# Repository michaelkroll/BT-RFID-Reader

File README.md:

BT-RFID-Reader
==============

BT-RFID-Reader Eagle design files, Arduino Sketch, WT-12 Config and 3D Enclosure files

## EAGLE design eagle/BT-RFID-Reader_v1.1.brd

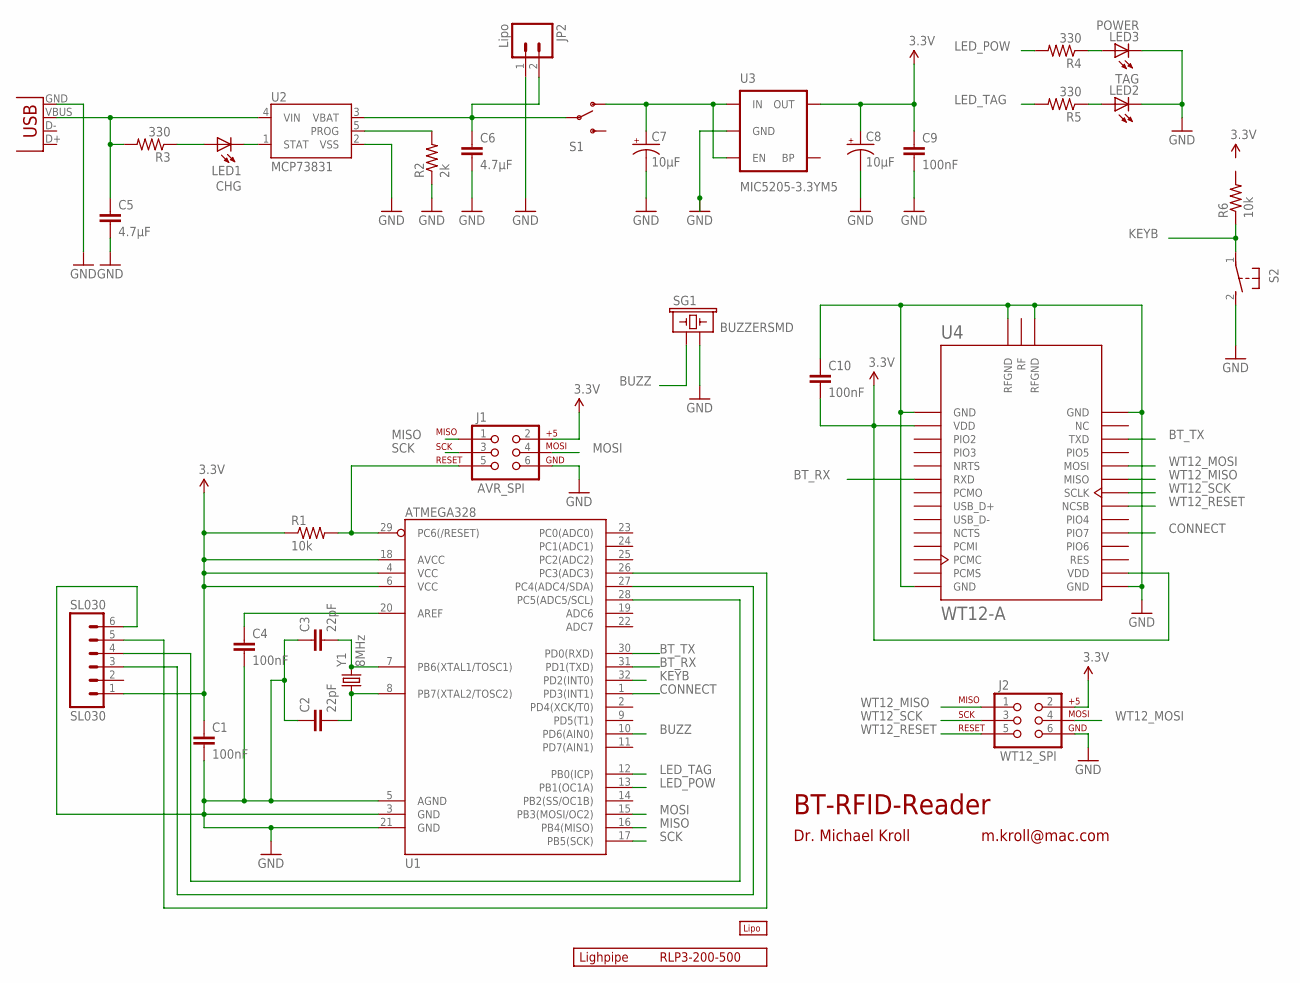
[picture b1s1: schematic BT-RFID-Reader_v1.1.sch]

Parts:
C1, C4, C9, C10: 100nF; 1206
C2, C3: 22pF; 1206
C5, C6: 4.7µF; 1206
C7, C8: 10µF; EIA3216
J1: AVR_SPI; 2X3
J2: WT12_SPI; 2X3
JP2: Lipo; JST-2-SMD
LED1: CHG; LED-1206
LED2: TAG; LED-1206-YELLOW
LED3: POWER; LED-1206-GREEN
R1, R6: 10k; 0805
R2: 2k; 0805
R3, R4, R5: 330; 0805
S1: SWITCH-SPSTSMD2; SWITCH-SPDT-SMD
S2: 31-XX; B3F-31XX
SG1: BUZZERSMD; BUZZER-CMT1603
SL030: SL030
U1: ATMEGA328; TQFP32-08
U2: MCP73831; SOT23-5
U3: MIC5205-3.3YM5; SOT23-5
U4: WT12-A
U$1: LIPO-OUTLINE1000; LIPO-1000
U$2: RLP3-200-500-OUTLINERLP3-200-500; RLP3-200-500
X1: USB-MICROB
Y1: 8MHz; HC49UP

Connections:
3.3V: C1.1, C8.A (+), C9.1, C10.2, J1.2, J2.2, R1.1, SL030.1 (VDD), U1.4 (VCC), U1.6 (VCC), U1.18 (AVCC), U3.5 (OUT), U4.VDD1 (VDD), U4.VDD2 (VDD)
BT_RX: U1.31 (PD1(TXD)), U4.RXD
BT_TX: U1.30 (PD0(RXD)), U4.TXD
BUZZ: SG1.P$1 (1), U1.10 (PD6(AIN0))
CONNECT: U1.1 (PD3(INT1)), U4.PIO7
GND: C1.2, C2.1, C3.1, C4.2, C5.2, C6.2, C7.C (-), C8.C (-), C9.2, C10.1, J1.6, J2.6, JP2.1, LED2.C, LED3.C, R2.1, S2.2 (S), SG1.P$2 (2), SL030.6 (GND), U1.3 (GND), U1.5 (AGND), U1.21 (GND), U2.2 (VSS), U3.2 (GND), U4.GND1 (GND), U4.GND2 (GND), U4.GND3 (GND), U4.GND4 (GND), U4.RFGND1 (RFGND), U4.RFGND2 (RFGND), X1.GND
KEYB: R6.1, S2.1, U1.32 (PD2(INT0))
LED_POW: R4.2, U1.13 (PB1(OC1A))
LED_TAG: R5.2, U1.12 (PB0(ICP))
MISO: J1.1, U1.16 (PB4(MISO))
MOSI: J1.4, U1.15 (PB3(MOSI/OC2))
unnamed: C2.2, U1.8 (PB7(XTAL2/TOSC2)), Y1.1
unnamed: SL030.4 (SLC), U1.28 (PC5(ADC5/SCL))
unnamed: SL030.3 (SDA), U1.27 (PC4(ADC4/SDA))
unnamed: SL030.5 (OUT), U1.26 (PC3(ADC3))
unnamed: C3.2, U1.7 (PB6(XTAL1/TOSC1)), Y1.2
unnamed: C5.1, R3.2, U2.4 (VIN), X1.VBUS
unnamed: C4.1, U1.20 (AREF)
unnamed: J1.5, R1.2, U1.29 (PC6(/RESET))
unnamed: R2.2, U2.5 (PROG)
unnamed: C6.1, JP2.2, S1.2, U2.3 (VBAT)
unnamed: C7.A (+), S1.1 (O), U3.1 (IN), U3.3 (EN)
unnamed: LED1.A, R3.1
unnamed: LED1.C, U2.1 (STAT)
unnamed: LED3.A, R4.1
unnamed: LED2.A, R5.1
SCK: J1.3, U1.17 (PB5(SCK))
WT12_MISO: J2.1, U4.MISO
WT12_MOSI: J2.4, U4.MOSI
WT12_RESET: J2.5, U4.NCSB
WT12_SCK: J2.3, U4.SCLK

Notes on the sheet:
BT-RFID-Reader
Dr. Michael Kroll
m.kroll@mac.com

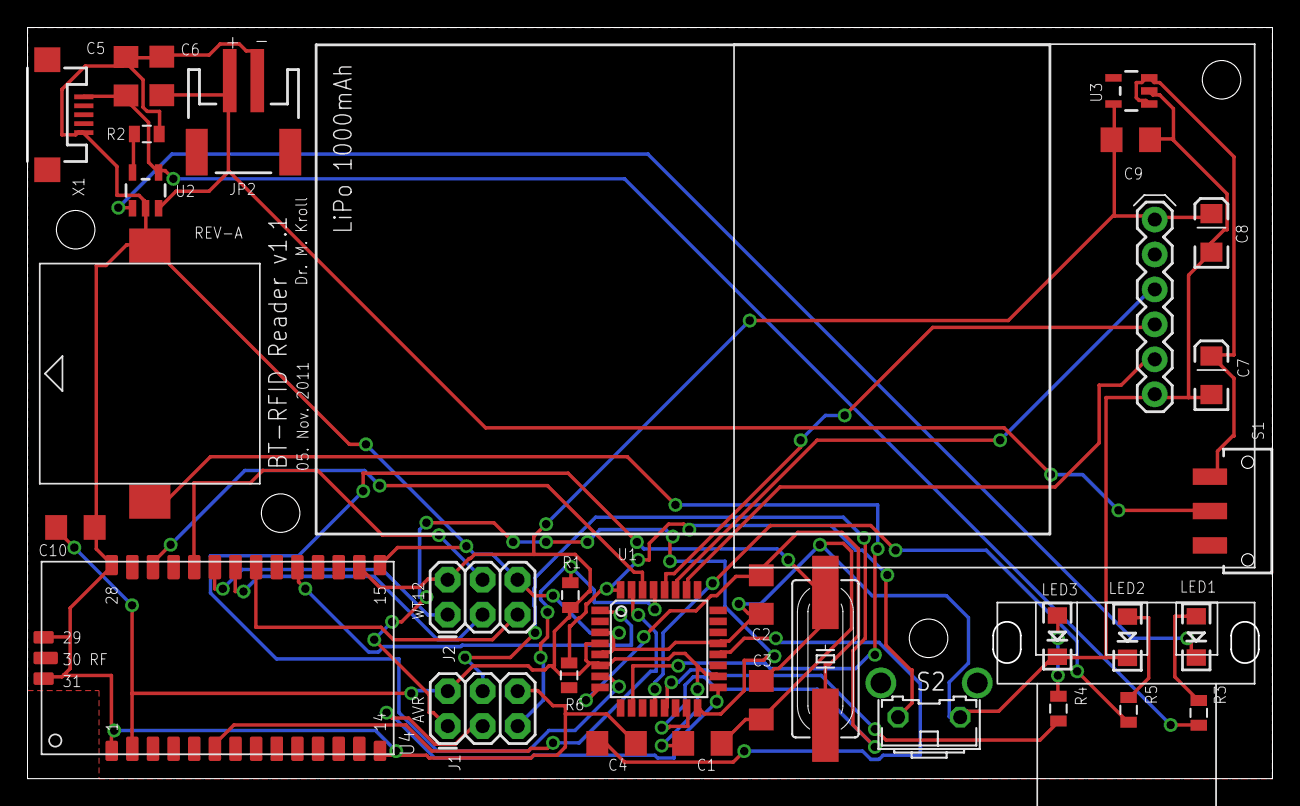
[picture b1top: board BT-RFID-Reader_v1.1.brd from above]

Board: 2 copper layers, 90.5 x 54.6 mm, 34 parts (0 on the bottom side), 31 nets.

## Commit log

2013-07-02 Initial commit of all files.
2013-07-02 Sketchup Model added
